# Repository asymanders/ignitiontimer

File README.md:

# Ignition timer

A digital ignition timer for the Matra Murena 2.2 and possibly other cars.

# Background

I started this project for my matra Murena 2.2 because I wanted to be able to time the ignition precisely. The Murena 2.2 was delivered from factory with a diagnostic connector fitted on the engine which had connections to a crank sensor device. The diagnostic connector also had other connections, e.g. to the alternator and sensors on the engine, and the ignition coil circuit from the ignition module. By measuring the time between the crank sensor signal and the ignition coil signal adjusting for the RPM, it would be possible to measure the advance precisely. 

A device that does this is briefly described in one of the original workshop manuals for the engine, however, nobody I've talked to have ever seen such a device, and I've started to doubt whether it existed at all. Also, documentation of the sensor is not available anywhere, so both the device and the sensor remained a mystery.

The sensor fitted looks like a normal, modern sensor, but turned out to be a little odd. Crank sensors are usually either of the Hall-type or pre-magnetized with a permanent magnet. This sensor is more like an inductive proximity sensor with no permanent magnet, but just a coil on what appears to be a ferrite core. It has a rather low DC resistance of about 50 Ohm. The sensor is fitted close to the flywheel which contains two indents, one at TDC and one at TDC + 180 degrees.

# Scope

This project describes the hardware and software of an analogue detector and Microprocessor based device which connects via the Murena diagnostic connector to the sensor and the ignition coil wires,  measures the signals, calculates the RPM and ignition advance, and displays the values in two rows of 7 segment displays. It also has provision for a serial port so that the values can be downloaded to a PC while the engine is running, and subsequently analyzed.

I've designed the device with a classic touch using my favorite MCU, the 8052. It's old and simple, but I wanted to justify that the device could have been made in the 1980's when the car was new. The circuit and PCB is designed in KiCad. The code consists of a single source file written in C for the SDCC compiller. The code is making well use of the three timers to run all the functions of the board, but the code is small and the 8K flahs ROM is far from used. Many of the 256 bytes of RAM are also in surplus.

The analogue section of the board is built around a differential amplifier and acomparator. I've DC-biased the sensor to create a permanent magnetic field which is then disturbed by the flywheel indent. Another comparator (actually the other half of the same IC) is used to detect ignition signals.

# Project history

I started the project in 2023, prototyping ways of making the analogue section. By the end of 2024, I have it working on the engine. The current PCB has several layout issues and I will make an updated version. It's also made for a specific TEKO box which I'm not sure is available from TEKO any more (it is still in stock from my preferred parts dealer).

The is thus still work-in-progress. 

The design is open source. 

# License

Copyright (c) 2024 Anders Dinsen anders@dinsen.net - All rights reserved.

Permission to use, copy, modify, and/or distribute this software for any purpose with or without fee is hereby granted.

THE SOFTWARE IS PROVIDED "AS IS" AND THE AUTHOR DISCLAIMS ALL WARRANTIES WITH REGARD TO THIS SOFTWARE INCLUDING ALL IMPLIED WARRANTIES OF MERCHANTABILITY AND FITNESS. IN NO EVENT SHALL THE AUTHOR BE LIABLE FOR ANY SPECIAL, DIRECT, INDIRECT, OR CONSEQUENTIAL DAMAGES OR ANY DAMAGES WHATSOEVER RESULTING FROM LOSS OF USE, DATA OR PROFITS, WHETHER IN AN ACTION OF CONTRACT, NEGLIGENCE OR OTHER TORTIOUS ACTION, ARISING OUT OF OR IN CONNECTION WITH THE USE OR PERFORMANCE OF THIS SOFTWARE.

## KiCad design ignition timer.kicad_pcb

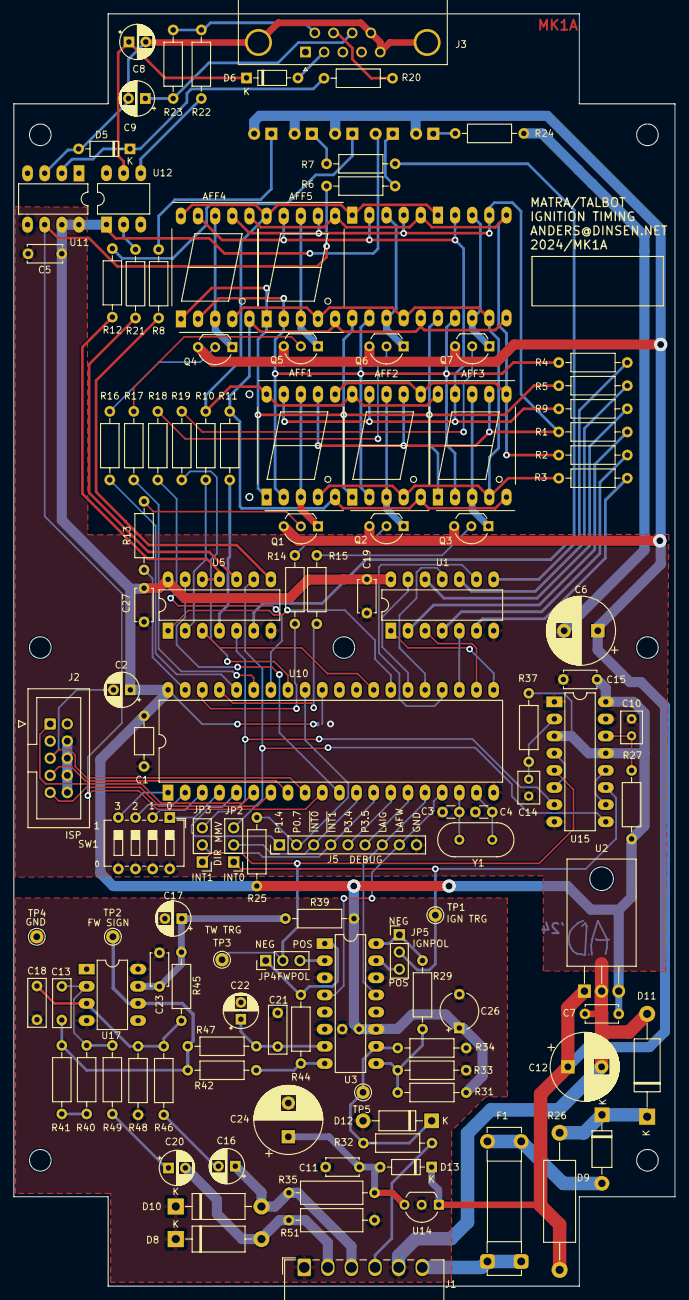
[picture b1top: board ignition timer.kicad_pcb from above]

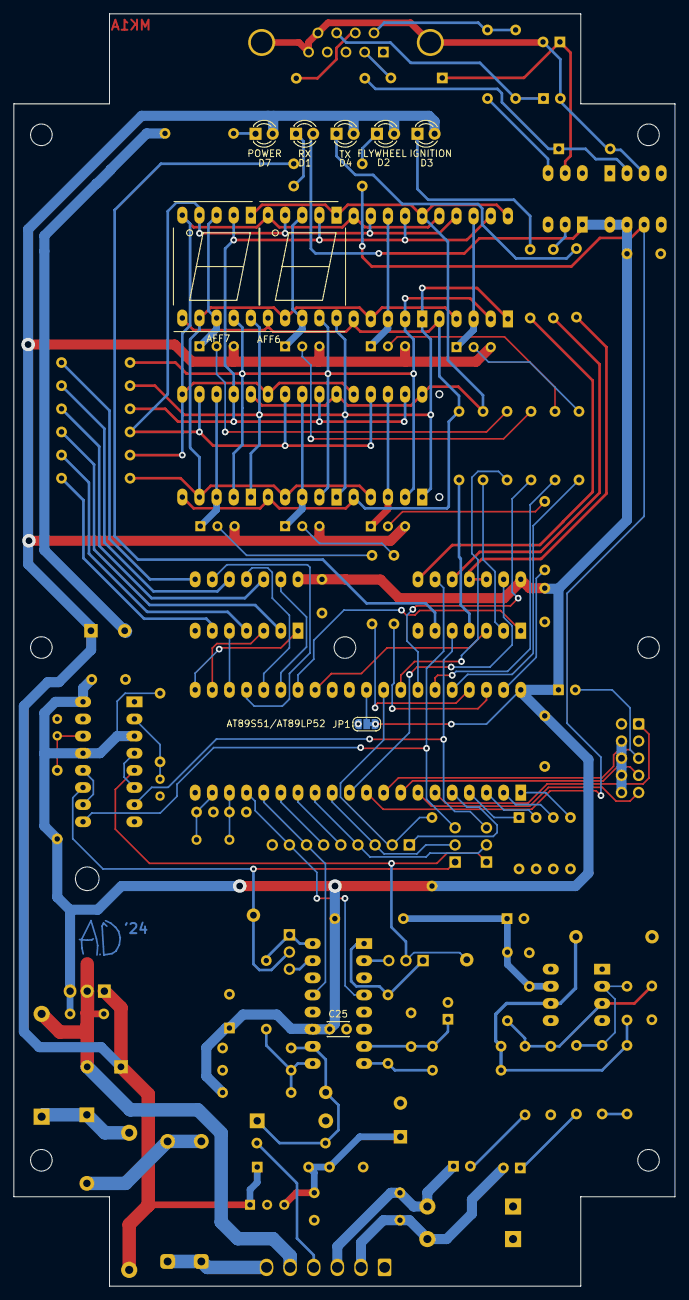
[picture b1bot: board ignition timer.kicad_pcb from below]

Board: 2 copper layers, 98.0 x 188.6 mm, 126 parts (9 on the bottom side), 116 nets.

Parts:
AFF1, AFF2, AFF3, AFF4, AFF5, AFF6, AFF7: LTS-6960HR; 7SegmentLED_LTS6760_LTS6780
C1: 100N; C_Axial_L3.8mm_D2.6mm_P7.50mm_Horizontal
C2: 1U/63V; CP_Radial_D5.0mm_P2.50mm
C3, C4: 33P; C_Disc_D3.0mm_W1.6mm_P2.50mm
C5: 100N; C_Disc_D5.0mm_W2.5mm_P5.00mm
C6, C12, C24: 470U/25V; CP_Radial_D10.0mm_P5.00mm
C7, C11, C15, C19, C23, C27: 100N; C_Disc_D4.7mm_W2.5mm_P5.00mm
C8, C9: 4U7/63V; CP_Radial_D5.0mm_P2.50mm
C10, C14: 10N; C_Rect_L4.6mm_W3.0mm_P2.50mm_MKS02_FKP02
C13, C18: 10N MKT; C_Rect_L7.0mm_W2.5mm_P5.00mm
C16, C20: 22U/25V; CP_Radial_D5.0mm_P2.50mm
C17: 33U; CP_Radial_D5.0mm_P2.50mm
C21: 10N POLY; C_Rect_L7.0mm_W2.5mm_P5.00mm
C22: 47U/25V; CP_Radial_D5.0mm_P2.50mm
C25: 100N; C_Disc_D3.0mm_W2.0mm_P2.50mm
C26: 10uF/16V TANTAL; CP_Radial_Tantal_D5.5mm_P5.00mm
D1: RX; LED_D3.0mm
D2: FLYWHEEL; LED_D3.0mm
D3: IGNITION; LED_D3.0mm
D4: TX; LED_D3.0mm
D5, D6, D13: 1N4148; D_DO-35_SOD27_P7.62mm_Horizontal
D7: POWER; LED_D3.0mm
D8, D10: TRANSIENTDIODE 13V; D_DO-15_P12.70mm_Horizontal
D9: 1N4007; D_DO-41_SOD81_P10.16mm_Horizontal
D11: TRANSIENTDIODE 15V/600W; D_DO-15_P15.24mm_Horizontal
D12: 4V7/1.3W; D_DO-41_SOD81_P10.16mm_Horizontal
F1: Fuse; Fuseholder_Clip-5x20mm_Bel_FC-203-22_Lateral_P17.80x5.00mm_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
J1: Conn_01x06; Wago_734-166_1x06_P3.50mm_Horizontal
J2: ISP; IDC-Header_2x05_P2.54mm_Vertical
J3: DB9_Female_MountingHoles; DSUB-9_Female_Horizontal_P2.77x2.84mm_EdgePinOffset7.70mm_H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
J5: DEBUG; PinHeader_1x09_P2.54mm_Vertical
JP1: AT89S51/AT89LP52; SolderJumper-3_P1.3mm_Bridged12_RoundedPad1.0x1.5mm_NumberL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
JP2: INT0; PinHeader_1x03_P2.54mm_Vertical
JP3: INT1; PinHeader_1x03_P2.54mm_Vertical
JP4: FWPOL; PinHeader_1x03_P2.54mm_Vertical
JP5: IGNPOL; PinHeader_1x03_P2.54mm_Vertical
Q1, Q2, Q3, Q4, Q5, Q6, Q7: BC557; TO-92_Inline_Wide
R1, R2, R3, R4, R5, R7, R8, R9, R10, R11, R12, R24: 470; R_Axial_DIN0207_L6.3mm_D2.5mm_P10.16mm_Horizontal
R6, R21: 270; R_Axial_DIN0207_L6.3mm_D2.5mm_P10.16mm_Horizontal
R13, R14, R15, R16, R17, R18, R19, R29, R46, R49: 10K; R_Axial_DIN0207_L6.3mm_D2.5mm_P10.16mm_Horizontal
R20, R31, R32, R33: 1K; R_Axial_DIN0207_L6.3mm_D2.5mm_P10.16mm_Horizontal
R22, R42: 100; R_Axial_DIN0207_L6.3mm_D2.5mm_P10.16mm_Horizontal
R23, R34: 1K5; R_Axial_DIN0207_L6.3mm_D2.5mm_P10.16mm_Horizontal
R25: 100K; R_Axial_DIN0207_L6.3mm_D2.5mm_P10.16mm_Horizontal
R26: 1R 1W; R_Axial_DIN0414_L11.9mm_D4.5mm_P20.32mm_Horizontal
R27, R37: 220K; R_Axial_DIN0207_L6.3mm_D2.5mm_P10.16mm_Horizontal
R35, R51: 100/1W; R_Axial_DIN0309_L9.0mm_D3.2mm_P12.70mm_Horizontal
R39: 33; R_Axial_DIN0207_L6.3mm_D2.5mm_P10.16mm_Horizontal
R40: 430; R_Axial_DIN0207_L6.3mm_D2.5mm_P10.16mm_Horizontal
R41: 24K; R_Axial_DIN0207_L6.3mm_D2.5mm_P10.16mm_Horizontal
R44: 33K; R_Axial_DIN0207_L6.3mm_D2.5mm_P10.16mm_Horizontal
R45: 51K; R_Axial_DIN0207_L6.3mm_D2.5mm_P10.16mm_Horizontal
R47: 680; R_Axial_DIN0207_L6.3mm_D2.5mm_P10.16mm_Horizontal
R48: 47K; R_Axial_DIN0207_L6.3mm_D2.5mm_P10.16mm_Horizontal
SW1: SW_DIP_x04; SW_DIP_SPSTx04_Slide_6.7x11.72mm_W7.62mm_P2.54mm_LowProfile
TP1: IGN TRG; Pin_D1.0mm_L10.0mm
TP2: FW SIGN; Pin_D1.0mm_L10.0mm
TP3: TW TRG; Pin_D1.0mm_L10.0mm
TP4: GND; Pin_D1.0mm_L10.0mm
TP5: IGN IN; Pin_D1.0mm_L10.0mm
U1, U5: 7416; DIP-14_W7.62mm_LongPads
U2: LM7805_TO220; TO-220-3_Horizontal_TabDown
U3: MAX912CPE; DIP-16_W7.62mm_LongPads
U10: AT89S51-24PI; DIP-40_W15.24mm_LongPads
U11: 6N137; DIP-8_W7.62mm_LongPads
U12: 4N37; DIP-6_W7.62mm_LongPads
U14: LM78L09; TO-92_Inline_Wide
U15: 74HCT4538; DIP-16_W7.62mm_LongPads
U17: TLC271; DIP-8_W7.62mm_LongPads
Y1: 11.059200 MHz; Crystal_HC49-U_Vertical

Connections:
+9V: C11.2, C24.1, D13.2 (A), R35.1, U14.3 (VO)
+12V: C6.1, C12.1, D2.2 (A), D3.2 (A), D4.2 (A), D7.2 (A), D13.1 (K), Q1.3 (E), Q2.3 (E), Q3.3 (E), Q4.3 (E), Q5.3 (E), Q6.3 (E), Q7.3 (E), R26.1, U2.1 (VI), U14.1 (VI)
/A: AFF1.7 (a), AFF2.7 (a), AFF3.7 (a), AFF4.7 (a), AFF5.7 (a), AFF6.7 (a), AFF7.7 (a), R1.2
/B: AFF1.6 (b), AFF2.6 (b), AFF3.6 (b), AFF4.6 (b), AFF5.6 (b), AFF6.6 (b), AFF7.6 (b), R2.1
/C: AFF1.4 (c), AFF2.4 (c), AFF3.4 (c), AFF4.4 (c), AFF5.4 (c), AFF6.4 (c), AFF7.4 (c), R3.1
/CIRCUIT 10 (IGNITION): J1.4, R32.2
/D: AFF1.2 (d), AFF2.2 (d), AFF3.2 (d), AFF4.2 (d), AFF5.2 (d), AFF6.2 (d), AFF7.2 (d), R4.1
/DP: AFF1.5 (DP), AFF2.5 (DP), AFF3.5 (DP), AFF4.5 (DP), AFF5.5 (DP), AFF6.5 (DP), AFF7.5 (DP), R11.1
/E: AFF1.1 (e), AFF2.1 (e), AFF3.1 (e), AFF4.1 (e), AFF5.1 (e), AFF6.1 (e), AFF7.1 (e), R5.1
/F: AFF1.9 (f), AFF2.9 (f), AFF3.9 (f), AFF4.9 (f), AFF5.9 (f), AFF6.9 (f), AFF7.9 (f), R9.1
/G: AFF1.10 (g), AFF2.10 (g), AFF3.10 (g), AFF4.10 (g), AFF5.10 (g), AFF6.10 (g), AFF7.10 (g), R10.1
/LATCH FW: J5.8, U3.4 (LATCH), U10.17 (P3.7/~RD)
/LATCH IGN: J5.7, U3.13 (LATCH), U10.16 (P3.6/~WR)
/MISO: J2.9, U10.7 (P1.6/MISO)
/MOSI: J2.1, U10.6 (P1.5/MOSI)
/RST: C2.2, J2.5, U10.9 (RST)
/SCK: J2.7, U10.8 (P1.7/SCK)
/SENSOR+: C16.1, D10.2 (A2), J1.3, R35.2
/SENSOR-: C20.2, D8.2 (A2), J1.2, R51.1
/~CA0: R13.1, U10.39 (P0.0/AD0)
/~CA1: R14.1, U10.38 (P0.1/AD1)
/~CA2: R15.1, U10.37 (P0.2/AD2)
/~CA3: R16.1, U10.36 (P0.3/AD3)
/~CA4: R17.2, U10.35 (P0.4/AD4)
/~CA5: R18.2, U10.34 (P0.5/AD5)
/~CA6: R19.1, U10.33 (P0.6/AD6)
/~EA/VPP: JP1.2 (C), U10.31 (~EA/VPP)
/~FWTRG: JP3.1 (A), JP4.2 (C), TP3.1, U15.5 (Clk-)
/~IGNTRG: JP2.1 (A), JP5.2 (C), TP1.1, U15.11 (Clk-)
/~INT0: J5.3, JP2.2 (C), U10.12 (P3.2/~INT0)
/~INT1: J5.4, JP3.2 (C), U10.13 (P3.3/~INT1)
GND: C1.2, C3.1, C4.1, C5.2, C6.2, C7.2, C10.2, C11.1, C12.2, C14.2, C15.2, C17.2, C18.1, C19.2, C21.2, C22.2, C23.2, C24.2, C25.2, C26.2, C27.2, D8.1 (A1), D10.1 (A1), D11.2 (A2), D12.2 (A), J1.1, J1.5, J2.4, J2.6, J2.8, J2.10, J5.9, JP1.3 (B), R24.1, R33.1, R34.2, R48.2, R51.2, SW1.5, SW1.6, SW1.7, SW1.8, TP4.1, U1.7 (GND), U2.2 (GND), U3.3 (GND), U3.6 (V-), U3.14 (GND), U5.7 (GND), U10.20 (GND), U11.5 (GND), U14.2 (GND), U15.1 (Cx), U15.8 (VSS), U15.15 (Cx), U17.4 (V-), U17.8 (BIAS)
unnamed: C13.2, R41.1, R42.2, R47.2, TP2.1, U17.6
unnamed: C16.2, R46.2
unnamed: C20.1, R49.2
unnamed: D1.1 (K), R6.2
unnamed: D2.1 (K), R7.2
unnamed: D3.1 (K), R8.2
unnamed: D4.1 (K), R12.2
unnamed: C8.2, C9.2, D5.2 (A), J3.0 (PAD), J3.5, J3.9, U11.3 (C)
unnamed: D5.1 (K), R20.1, U11.2 (A)
unnamed: D6.2 (A), J3.2
unnamed: C8.1, D6.1 (K), U12.5
unnamed: D7.1 (K), R24.2
unnamed: D9.2 (A), F1.2
unnamed: D9.1 (K), D11.1 (A1), R26.2
unnamed: D12.1 (K), R32.1, R34.1, TP5.1, U3.10 (-)
unnamed: F1.1, J1.6
unnamed: J3.6, R22.2, R23.2
unnamed: J3.7, R20.2
unnamed: J5.1, U10.5 (P1.4)
unnamed: J5.2, R25.2, U10.32 (P0.7/AD7)
unnamed: J5.5, U10.14 (P3.4/T0)
unnamed: J5.6, U10.15 (P3.5/T1)
unnamed: JP2.3 (B), U5.9, U15.9 (~Q)
unnamed: JP3.3 (B), U5.5, U15.7 (~Q)
unnamed: JP4.1 (A), R44.1, U3.1 (Q)
unnamed: JP4.3 (B), U3.2 (~Q)
unnamed: JP5.1 (A), R29.1, U3.16 (Q)
unnamed: JP5.3 (B), U3.15 (~Q)
unnamed: Q1.2 (B), R13.2
unnamed: AFF1.3 (C.A.), AFF1.8 (C.A.), Q1.1 (C)
unnamed: Q2.2 (B), R14.2
unnamed: AFF2.3 (C.A.), AFF2.8 (C.A.), Q2.1 (C)
unnamed: Q3.2 (B), R15.2
unnamed: AFF3.3 (C.A.), AFF3.8 (C.A.), Q3.1 (C)
unnamed: Q4.2 (B), R16.2
unnamed: AFF4.3 (C.A.), AFF4.8 (C.A.), Q4.1 (C)
unnamed: Q5.2 (B), R17.1
unnamed: AFF5.3 (C.A.), AFF5.8 (C.A.), Q5.1 (C)
unnamed: Q6.2 (B), R18.1
unnamed: AFF6.3 (C.A.), AFF6.8 (C.A.), Q6.1 (C)
unnamed: Q7.2 (B), R19.2
unnamed: AFF7.3 (C.A.), AFF7.8 (C.A.), Q7.1 (C)
unnamed: R1.1, U1.2
unnamed: R2.2, U1.4
unnamed: R3.2, U1.6
unnamed: R4.2, U1.8
unnamed: R5.2, U1.10
unnamed: R7.1, U5.6
unnamed: R8.1, U5.8
unnamed: R9.2, U1.12
unnamed: R10.2, U5.2
unnamed: R11.2, U5.4
unnamed: R12.1, U5.11, U5.12
unnamed: R21.1, U5.10
unnamed: R21.2, U12.2
unnamed: R22.1, U12.4
unnamed: R40.1, R41.2
unnamed: R42.1, R44.2, U3.8 (+)
unnamed: C21.1, C22.1, R47.1, U3.7 (-)
unnamed: R29.2, R31.1, R33.2, U3.9 (+)
unnamed: SW1.4, U10.1 (P1.0)
unnamed: SW1.3, U10.2 (P1.1)
unnamed: SW1.2, U10.3 (P1.2)
unnamed: SW1.1, U10.4 (P1.3)
unnamed: U1.1, U10.21 (P2.0/A8)
unnamed: U1.3, U10.22 (P2.1/A9)
unnamed: U1.5, U10.23 (P2.2/A10)
unnamed: U1.9, U10.24 (P2.3/A11)
unnamed: U1.11, U10.25 (P2.4/A12)
unnamed: U1.13, U10.26 (P2.5/A13)
unnamed: U5.1, U10.27 (P2.6/A14)
unnamed: U5.3, U10.28 (P2.7/A15)
unnamed: R6.1, U10.10 (P3.0/RXD), U11.6 (VO)
unnamed: U5.13, U10.11 (P3.1/TXD)
unnamed: C4.2, U10.19 (XTAL1), Y1.1
unnamed: C3.2, U10.18 (XTAL2), Y1.2
unnamed: U15.4 (Clk+), U15.6 (Q)
unnamed: C14.1, R37.1, U15.2 (RxCx)
unnamed: U15.10 (Q), U15.12 (Clk+)
unnamed: C10.1, R27.1, U15.14 (RxCx)
unnamed: C18.2, R45.2, R46.1, R48.1, U17.3 (+)
unnamed: C13.1, R40.2, R49.1, U17.2 (-)
VCC: C1.1, C2.1, C5.1, C7.1, C15.1, C19.1, C25.1, C26.1, C27.1, D1.2 (A), JP1.1 (A), R25.1, R27.2, R31.2, R37.2, R39.1, U1.14 (VCC), U2.3 (VO), U3.11 (V+), U5.14 (VCC), U10.40 (VCC), U11.7 (EN), U11.8 (VCC), U12.1, U15.3 (R), U15.13 (R), U15.16 (VDD)
VSSA: C17.1, C23.1, R39.2, R45.1, U17.7 (V+)

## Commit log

2024-11-09 Update license
2024-11-09 Update license and target board configurations
2024-11-19 Fixed messed up flipped displays
